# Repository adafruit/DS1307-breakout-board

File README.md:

## Adafruit DS1307 Real Time Clock Assembled Breakout Board PCB

<a href="http://www.adafruit.com/products/3296"><br/>
Click here to purchase one from the Adafruit shop</a>

PCB files for the Adafruit DS1307 Real Time Clock Assembled Breakout Board. Format is EagleCAD schematic and board layout
* https://www.adafruit.com/product/3296

### Description

This is a great battery-backed real time clock (RTC) that allows your microcontroller project to keep track of time even if it is reprogrammed, or if the power is lost. Perfect for datalogging, clock-building, time stamping, timers and alarms, etc. The DS1307 is the most popular RTC - but it requires 5V power to work (although we've used it with 5V power and 3.3V logic successfully)

Works great with an [Arduino using our RTC library](https://github.com/adafruit/RTClib) or with a [Raspberry Pi (or similar single board linux computer)](https://learn.adafruit.com/adding-a-real-time-clock-to-raspberry-pi)

The DS1307 is simple and inexpensive but not a high precision device. It may lose or gain up to 2 seconds a day. For a high-precision, temperature compensated alternative, [please check out the DS3231 precision RTC](https://www.adafruit.com/products/3013). If you do not need a DS1307, or you need a 3.3V-power/logic capable RTC please check out our affordable [PCF8523 RTC breakout](http://www.adafruit.com/products/3295)

### License

Adafruit invests time and resources providing this open source design, please support Adafruit and open-source hardware by purchasing products from [Adafruit](https://www.adafruit.com)!

Designed by Limor Fried/Ladyada for Adafruit Industries.

Creative Commons Attribution/Share-Alike, all text above must be included in any redistribution. See license.txt for additional details.

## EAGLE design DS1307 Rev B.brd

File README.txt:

This is the PCB for the DS1307 Real Time Clock breakout board
Format is EagleCAD schematic and board layout

For more details, check out the product page at

   * http://www.adafruit.com/products/264
   * http://www.adafruit.com/products/3296

Adafruit invests time and resources providing this open source design, 
please support Adafruit and open-source hardware by purchasing 
products from Adafruit!

Designed by Adafruit Industries.  
Creative Commons Attribution, Share-Alike license, check license.txt for more information
All text above must be included in any redistribution

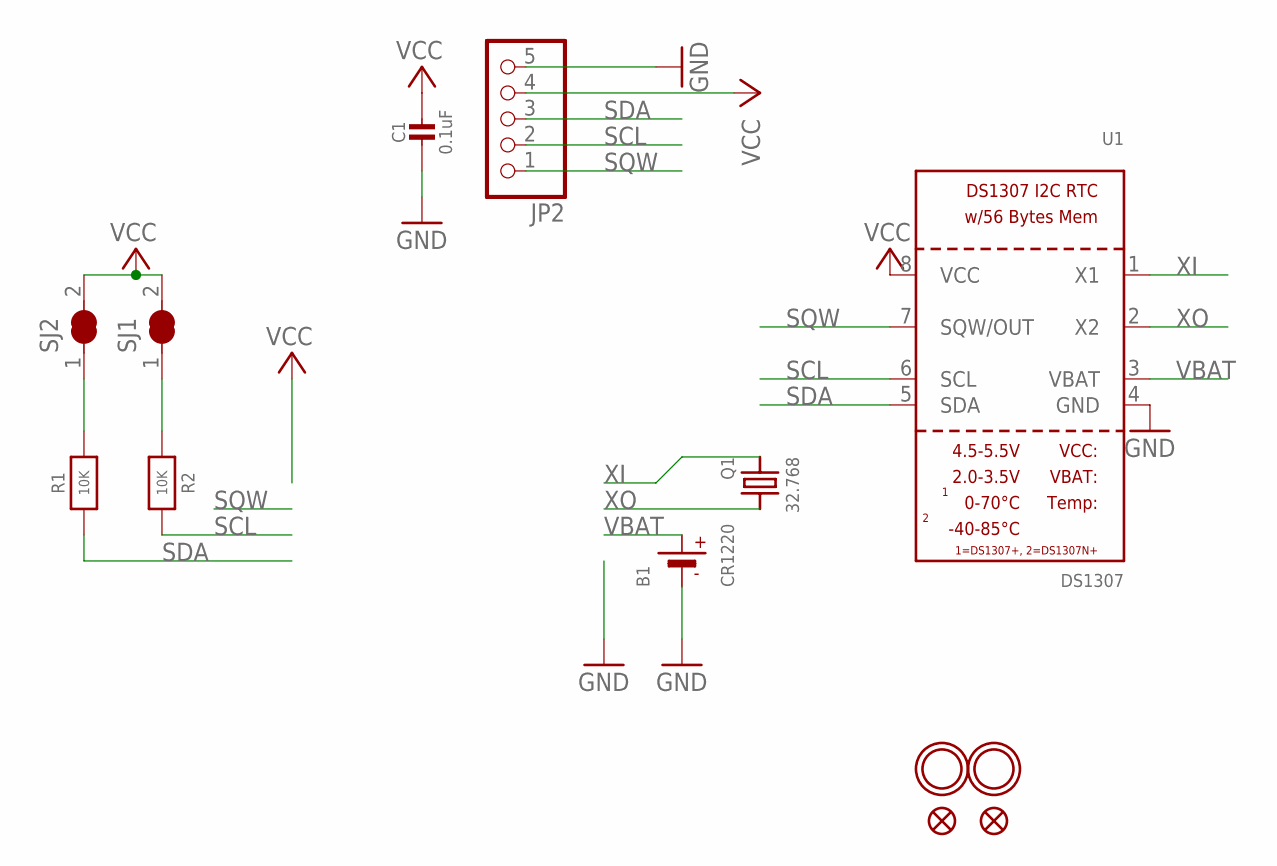
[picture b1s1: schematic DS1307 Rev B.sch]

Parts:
B1: CR1220
C1: 0.1uF; 0805-NO
FID1, FID2: FIDUCIAL""; FIDUCIAL_1MM
JP2: HEADER-1X576MIL; 1X05_ROUND_76
Q1: 32.768; CRYSTAL_8X3.8
R1, R2: 10K; 0805-NO
SJ1, SJ2: SOLDERJUMPER_CLOSED; SOLDERJUMPER_CLOSEDWIRE
U1: DS1307; SOIC8_150MIL
U$1, U$4: MOUNTINGHOLE2.0; MOUNTINGHOLE_2.0_PLATED

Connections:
GND: B1.-, C1.2, JP2.5, U1.4 (GND)
unnamed: R2.1, SJ1.1
unnamed: R1.2, SJ2.1
SCL: JP2.2, R2.2, U1.6 (SCL)
SDA: JP2.3, R1.1, U1.5 (SDA)
SQW: JP2.1, U1.7 (SQW/OUT)
VBAT: B1.+$1 (+), U1.3 (VBAT)
VCC: C1.1, JP2.4, SJ1.2, SJ2.2, U1.8 (VCC)
XI: Q1.P$1 (1), U1.1 (X1)
XO: Q1.P$4 (2), U1.2 (X2)

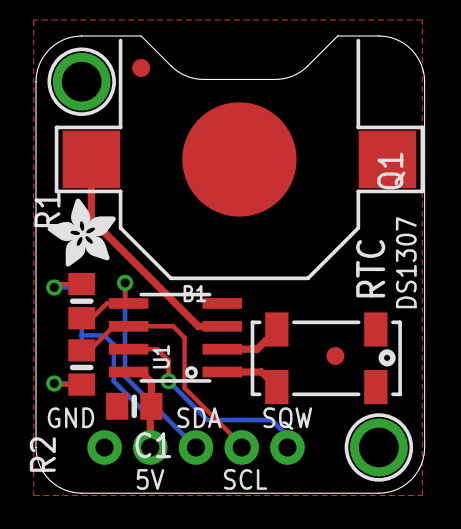
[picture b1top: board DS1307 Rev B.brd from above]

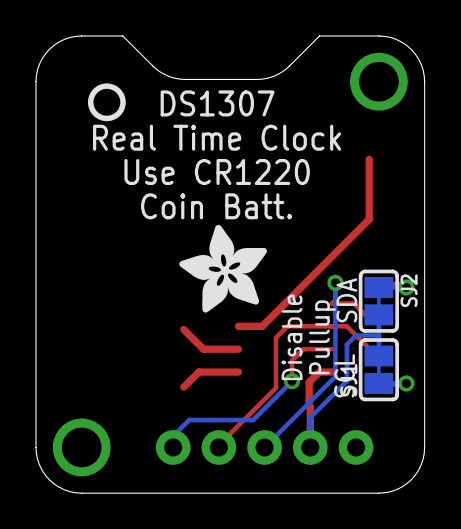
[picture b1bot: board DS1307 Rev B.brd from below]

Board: 2 copper layers, 21.6 x 25.4 mm, 16 parts (4 on the bottom side), 10 nets.

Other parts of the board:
U$2: ADAFRUIT_3.5MM
U$3: PCBFEAT-REV-040
U$5: ADAFRUIT_5MM

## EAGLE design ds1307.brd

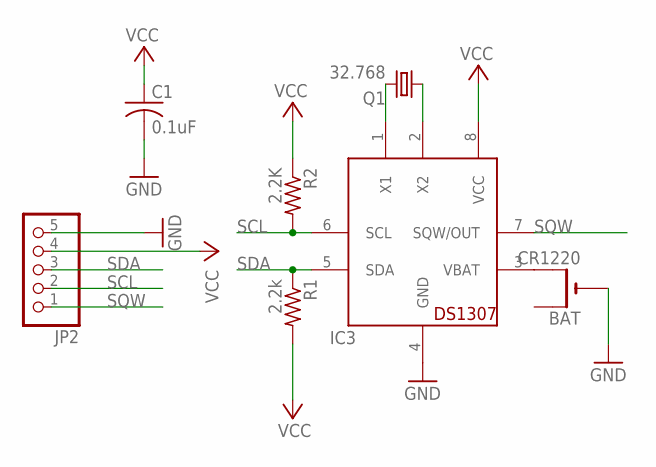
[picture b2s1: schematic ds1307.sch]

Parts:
BAT: CR1220; CR1220-THM
C1: 0.1uF; C025-025X050
IC3: DS1307; DIL08
JP2: PINHD-1X5; 1X05
Q1: 32.768; TC38H
R1: 2.2k; 0207/10
R2: 2.2K; 0207/10

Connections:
GND: BAT.-, C1.2, IC3.4 (GND), JP2.5
unnamed: IC3.1 (X1), Q1.2
unnamed: IC3.2 (X2), Q1.1
unnamed: BAT.+2 (+1), IC3.3 (VBAT)
SCL: IC3.6 (SCL), JP2.2, R2.2
SDA: IC3.5 (SDA), JP2.3, R1.1
SQW: IC3.7 (SQW/OUT), JP2.1
VCC: C1.1, IC3.8 (VCC), JP2.4, R1.2, R2.1

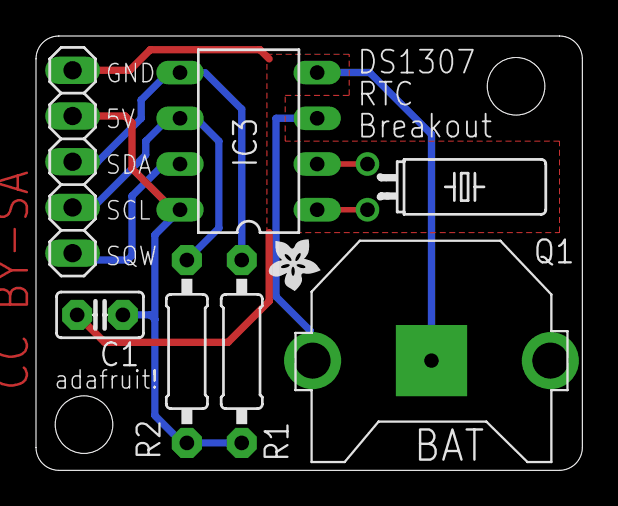
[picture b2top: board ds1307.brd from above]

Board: 2 copper layers, 30.4 x 24.1 mm, 8 parts (0 on the bottom side), 8 nets.

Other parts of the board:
U$1: ADAFRUIT200MIL

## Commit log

2010-07-26 Eagle files and a photo
2010-07-30 readme
2010-07-30 html?
2010-07-30 guess not :(
2011-12-19 .txt -> .md; make text H1
2014-07-28 with url!
2014-07-28 eagle 6!
2017-08-31 new rev!
2019-07-16 updated repo to match new cookiecutter
2019-07-16 typo fix

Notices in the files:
ds1307.brd:
CC BY-SA
parts and their libraries:
microbuilder: This work is placed in the public domain, and may be freely used for commercial and non-commercial work with the following conditions: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
